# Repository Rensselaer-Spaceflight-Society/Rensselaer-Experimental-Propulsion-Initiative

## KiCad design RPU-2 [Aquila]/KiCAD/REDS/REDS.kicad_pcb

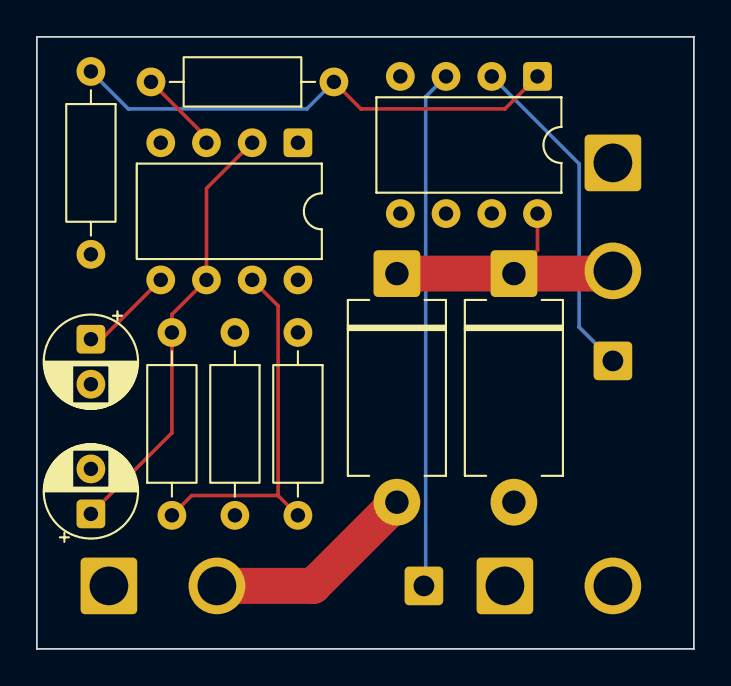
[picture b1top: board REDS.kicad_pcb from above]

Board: 4 copper layers, 36.5 x 34.0 mm, 16 parts (0 on the bottom side), 11 nets.

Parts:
C1: 1uF; CP_Radial_D5.0mm_P2.50mm
C2: 1nF; CP_Radial_D5.0mm_P2.50mm
D1, D2: 1N4148WT; D_DO-201_P12.70mm_Horizontal
J2: Our Power; SolderWire-1.5sqmm_1x02_P6mm_D1.7mm_OD3mm
J3: Reds Power; SolderWire-1.5sqmm_1x02_P6mm_D1.7mm_OD3mm
J4: Servo Signal Servo Power; SolderWire-1.5sqmm_1x02_P6mm_D1.7mm_OD3mm
J5: Our Signal; SolderWire-0.5sqmm_1x01_D0.9mm_OD2.1mm
J6: Signal; SolderWire-0.5sqmm_1x01_D0.9mm_OD2.1mm
R1: 10k; R_Axial_DIN0207_L6.3mm_D2.5mm_P10.16mm_Horizontal
R2: 1.5k; R_Axial_DIN0207_L6.3mm_D2.5mm_P10.16mm_Horizontal
R3: 2k; R_Axial_DIN0207_L6.3mm_D2.5mm_P10.16mm_Horizontal
R4: 1.8k; R_Axial_DIN0207_L6.3mm_D2.5mm_P10.16mm_Horizontal
R5: 1k; R_Axial_DIN0207_L6.3mm_D2.5mm_P10.16mm_Horizontal
U3: LM555xN; DIP-8_W7.62mm
U4: MAX4544; DIP-8_W7.62mm

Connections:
555out: R3.1, R5.1, U4.1 (NO)
+6.8V: D1.2 (A), J3.1, R1.1, R2.1, U3.4 (R), U3.8 (VCC), U4.7 (IN)
GND: C1.2, C2.2, J2.1, J3.2, J4.1, R1.2, R3.2, U3.1 (GND), U4.4 (GND)
unnamed: D1.1 (K), D2.1 (K), J4.2, U4.8 (V+)
unnamed: J6.1 (Pin_1_1), U4.2 (COM)
unnamed: C2.1, U3.5 (CV)
unnamed: R2.2, R4.1, U3.7 (DIS)
unnamed: R5.2, U3.3 (Q)
unnamed: C1.1, R4.2, U3.2 (TR), U3.6 (THR)
OurPower: D2.2 (A), J2.2
OurSignal: J5.1 (Pin_1_1), U4.3 (NC)

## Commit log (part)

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2026-04-26 Move RPU-1 things into RPU-1 Folder
2026-05-22 Fixing the names of the folders to be Windows Compatible
2026-05-22 Fixing the names of the folders to be Windows Compatible (#16)
2026-05-23 Creating subfolders for firmware
2026-05-23 Added subfolders for RPU2 + Firmware
2026-05-25 Added template project
2026-06-03 Create client and server code projects for radio testing
2026-06-03 set up initial files for radio testing.
2026-06-03 updated code to support C++ code.
